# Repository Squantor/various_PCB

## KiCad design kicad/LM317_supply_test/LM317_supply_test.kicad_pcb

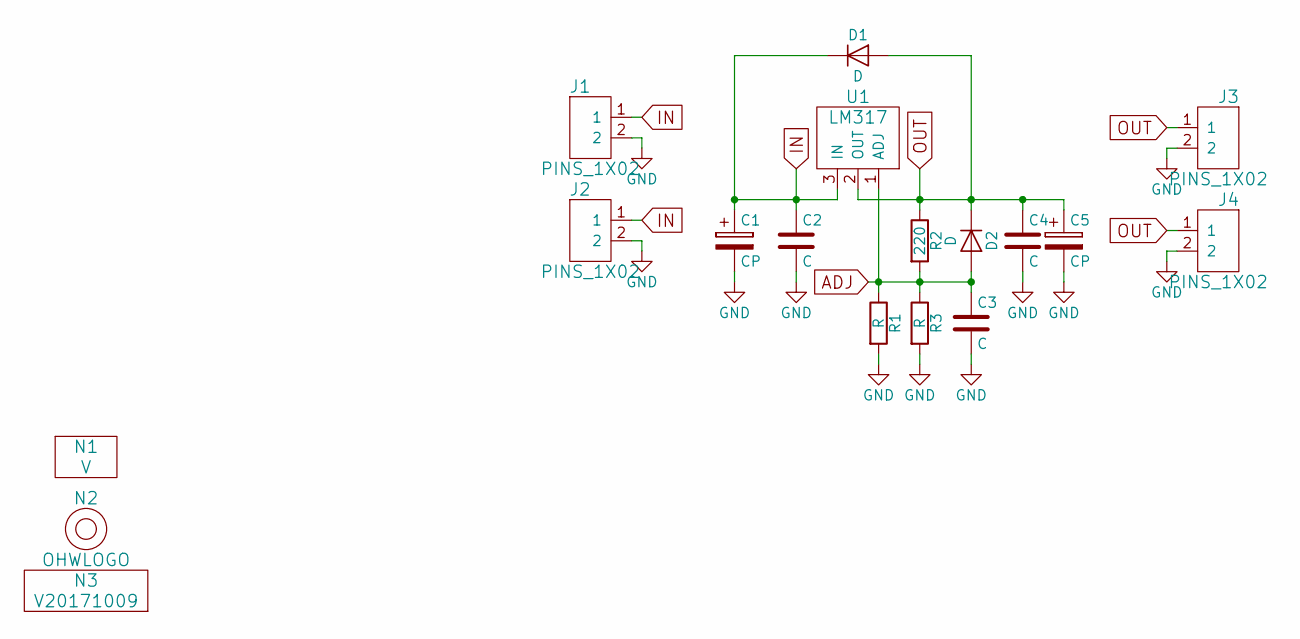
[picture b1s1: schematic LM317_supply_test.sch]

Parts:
C1, C5: CP; CPOL-05-06
C2, C3, C4: C; C_0805
D1, D2: D; MELF_D_0207
J1, J2, J3, J4: PINS_1X02; Header-0254-1X02-H010
N1: V; Label_Note_small
N2: OHWLOGO; OSHW-Symbol_6.7x6mm_SilkScreen
N3: V20171009; Label_version
R1, R3: R; R_0603_hand
R2: 220; R_0603_hand
U1: LM317; TO-263-D2PAK-3-3-viapad

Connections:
ADJ: C3.1, D2.2 (A), R1.1, R2.2, R3.1, U1.1 (ADJ)
GND: C1.2, C2.2, C3.2, C4.2, C5.2, J1.2, J2.2, J3.2, J4.2, R1.2, R3.2
IN: C1.1, C2.1, D1.1 (K), J1.1, J2.1, U1.3 (IN)
OUT: C4.1, C5.1, D1.2 (A), D2.1 (K), J3.1, J4.1, R2.1, U1.2 (OUT)

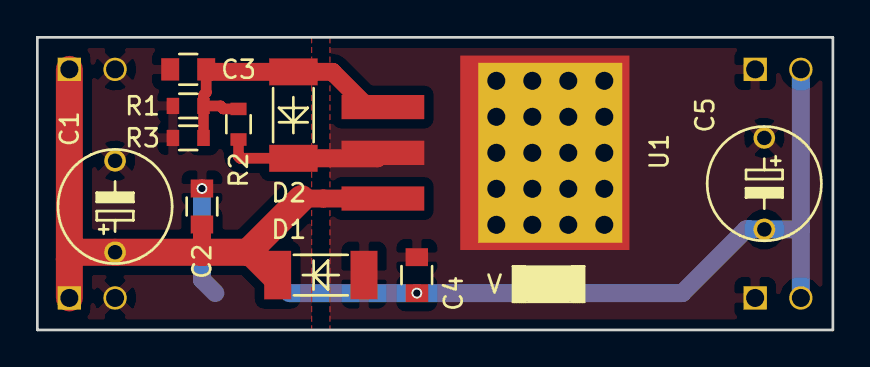
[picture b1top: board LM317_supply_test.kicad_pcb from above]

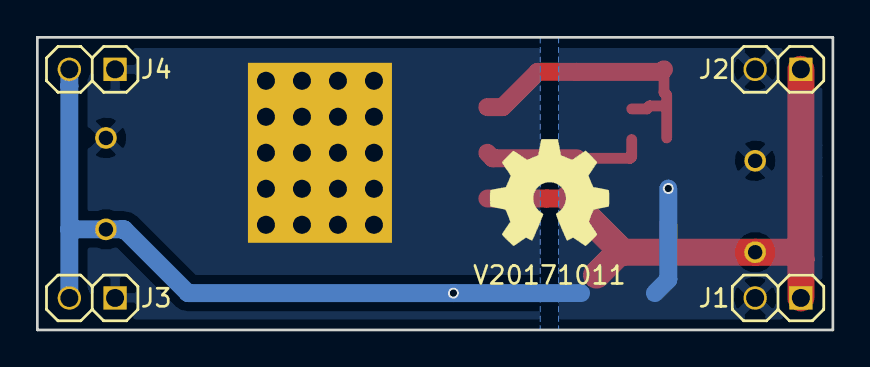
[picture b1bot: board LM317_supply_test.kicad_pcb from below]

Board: 2 copper layers, 44.2 x 16.3 mm, 18 parts (5 on the bottom side), 4 nets.

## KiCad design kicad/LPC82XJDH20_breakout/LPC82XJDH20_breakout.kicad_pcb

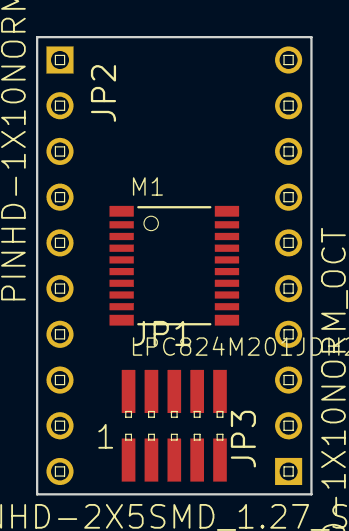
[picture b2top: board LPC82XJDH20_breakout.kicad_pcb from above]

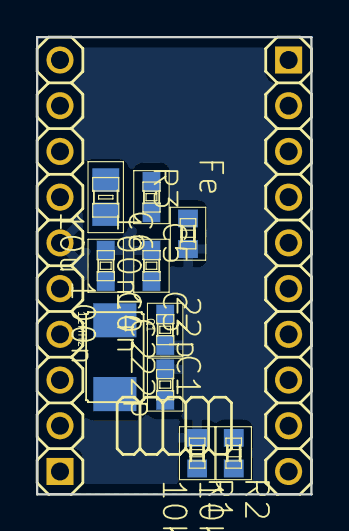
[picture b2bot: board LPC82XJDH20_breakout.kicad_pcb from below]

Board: 2 copper layers, 15.2 x 25.4 mm, 14 parts (10 on the bottom side), 20 nets, no tracks yet.

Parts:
C1, C2: 22p; SquantorRCL-C0603
C3: 10n; SquantorRCL-C0603
C4, C5: 100n; SquantorRCL-C0603
C6: 10u; SquantorRCL-C0805
JP1: PINHD-2X5SMD_1.27_SMD; SquantorConnectors-2X05_1.27_SMD
JP2, JP3: PINHD-1X10NORM_OCT; SquantorConnectors-1X10_NORMAL_OCT
M1: LPC824M201JDH20; SOT360
Q1: 12MHz; SquantorCrystal-CRYSTAL_5.0X3.2
R1, R2: 10k; SquantorRCL-R0603
R3: Fe; SquantorRCL-R0603

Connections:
GNDA: C5.2, C6.2, JP3.7, M1.17, R3.2
PIO0_0: JP3.9, M1.19
PIO0_1: JP3.2, M1.12
PIO0_2/SWDIO: JP1.1, JP2.8, M1.8, R2.2
PIO0_3/SWCLK: JP1.3, JP2.7, M1.7, R1.2
PIO0_4: JP2.6, M1.6
PIO0_5/reset: JP1.9, JP2.5, M1.5
PIO0_8: C1.1, JP3.4, M1.14, Q1.1
PIO0_9: C2.1, JP3.3, M1.13, Q1.2
PIO0_10: JP2.10, M1.10
PIO0_11: JP2.9, M1.9
PIO0_12: JP2.4, M1.4
PIO0_13: JP2.3, M1.3
PIO0_14: JP3.10, M1.20
PIO0_15: JP3.1, M1.11
PIO0_17: JP2.2, M1.2
PIO0_23: JP2.1, M1.1
VAA: C5.1, C6.1, JP3.8, M1.18
VDD: C3.2, C4.2, JP1.2, JP3.5, M1.15, R2.1
VSS: C1.2, C2.2, C3.1, C4.1, JP1.4, JP1.6, JP1.10, JP3.6, M1.16, R1.1, R3.1

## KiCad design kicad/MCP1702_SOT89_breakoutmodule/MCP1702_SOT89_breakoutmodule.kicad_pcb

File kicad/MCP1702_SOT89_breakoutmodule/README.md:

# MCP1702 breakout and module
This is a breakout for the MCP1702 LDO, it is breadboard friendly but two Molex Picoblade connectors make it also possible to use it in a cable. The MCP1702 has additional thermal vias and a large plane to help with power dissipation.

## TODO's
Still some things need to be done:
* schematic entry (Done)
* PCB layout (Done)
* Review with one night in between (Done)
* Produce at [OSHPARK](https://oshpark.com/shared_projects/njzrqEmi) (in progress)
* Assemble
* Test 
* update Readme.md with pictures and BOM
## BOM
TODO

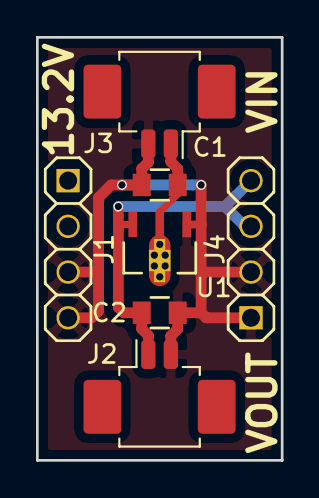
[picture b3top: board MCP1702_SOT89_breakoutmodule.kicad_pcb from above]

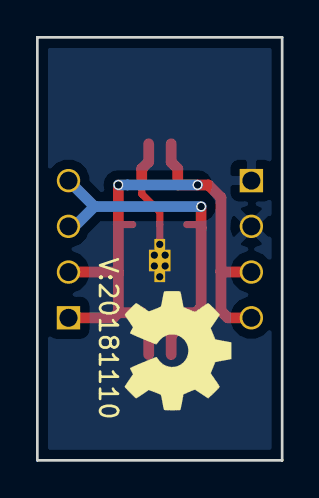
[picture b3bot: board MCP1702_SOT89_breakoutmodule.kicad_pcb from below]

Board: 2 copper layers, 13.6 x 23.5 mm, 9 parts (2 on the bottom side), 3 nets.

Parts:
C1, C2: C; C_0805
J1, J4: Conn_01x04; Header-0254-1X04-H010
J2, J3: Conn_01x02; Molex_PicoBlade_53261-0271_1x02-1MP_P1.25mm_Horizontal
N1: OHWLOGO; OSHW-Symbol_6.7x6mm_SilkScreen
N2: 20181110; Label_version
U1: MCP1702-MB; SOT89-ViaTab-Microchip-MB

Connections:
+12V: C1.1, J1.1, J1.2, J3.1, U1.2, U1.TAB
GND: C1.2, C2.2, J1.3, J1.4, J2.2, J3.2, J4.1, J4.2, U1.1
VDD: C2.1, J2.1, J4.3, J4.4, U1.3

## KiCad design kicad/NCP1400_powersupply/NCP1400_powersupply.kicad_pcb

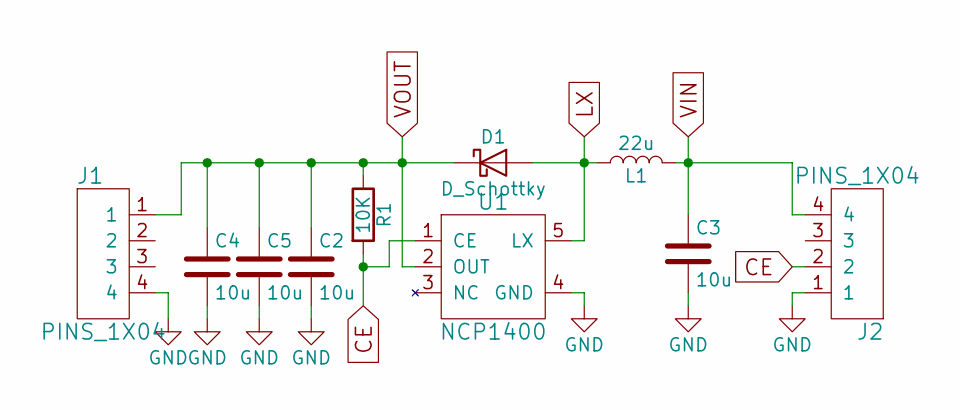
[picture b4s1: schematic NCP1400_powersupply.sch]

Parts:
C2, C3, C4, C5: 10u; C_0805
D1: D_Schottky; SOD-123-hand
J1, J2: PINS_1X04; Header-0254-1X04-H010
L1: 22u; TAIYO_YUDEN_NRS50XX
R1: 10K; R_0603_hand
U1: NCP1400; SN-SOT23-5

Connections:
CE: J2.2, R1.2, U1.1 (CE)
GND: C2.2, C3.2, C4.2, C5.2, J1.4, J2.1, U1.4 (GND)
LX: D1.2 (A), L1.1, U1.5 (LX)
VIN: C3.1, J2.4, L1.2
VOUT: C2.1, C4.1, C5.1, D1.1 (K), J1.1, R1.1, U1.2 (OUT)

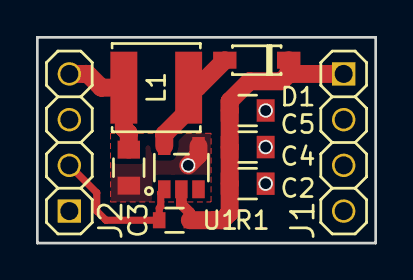
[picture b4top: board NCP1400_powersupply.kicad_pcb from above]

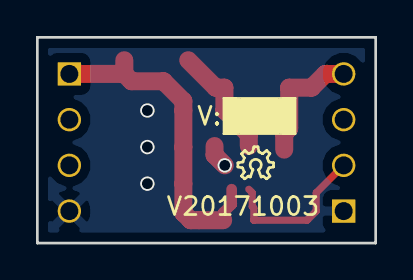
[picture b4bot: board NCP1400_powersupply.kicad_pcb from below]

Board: 2 copper layers, 18.8 x 11.4 mm, 13 parts (2 on the bottom side), 5 nets.

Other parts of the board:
N1: V20171003; Label_version
N2: OHWLOGO; ohw-logo-OSHW_6X70_NOTEXT
N3: V:; Label_Note_small

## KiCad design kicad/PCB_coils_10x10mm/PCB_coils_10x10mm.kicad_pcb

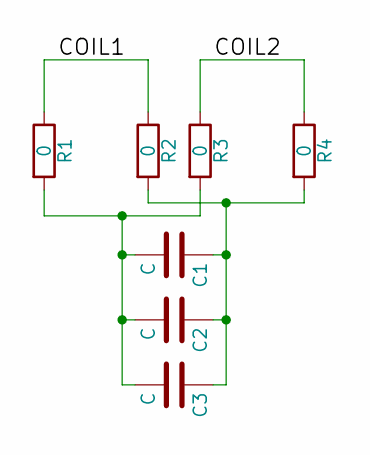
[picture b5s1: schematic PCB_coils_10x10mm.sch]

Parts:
C1, C2, C3: C; C_0805
R1, R2, R3, R4: 0; R_0603_hand

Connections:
/COIL1: R1.1, R2.1
/COIL2: R3.1, R4.1
unnamed: C1.1, C2.1, C3.1, R2.2, R4.2
unnamed: C1.2, C2.2, C3.2, R1.2, R3.2

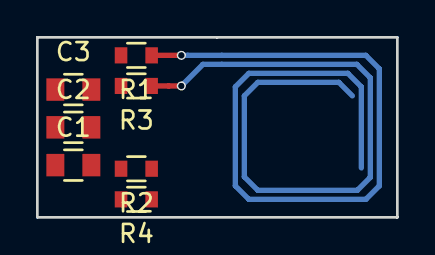
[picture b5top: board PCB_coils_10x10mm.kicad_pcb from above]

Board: 2 copper layers, 20.0 x 10.0 mm, 7 parts (0 on the bottom side), 4 nets.

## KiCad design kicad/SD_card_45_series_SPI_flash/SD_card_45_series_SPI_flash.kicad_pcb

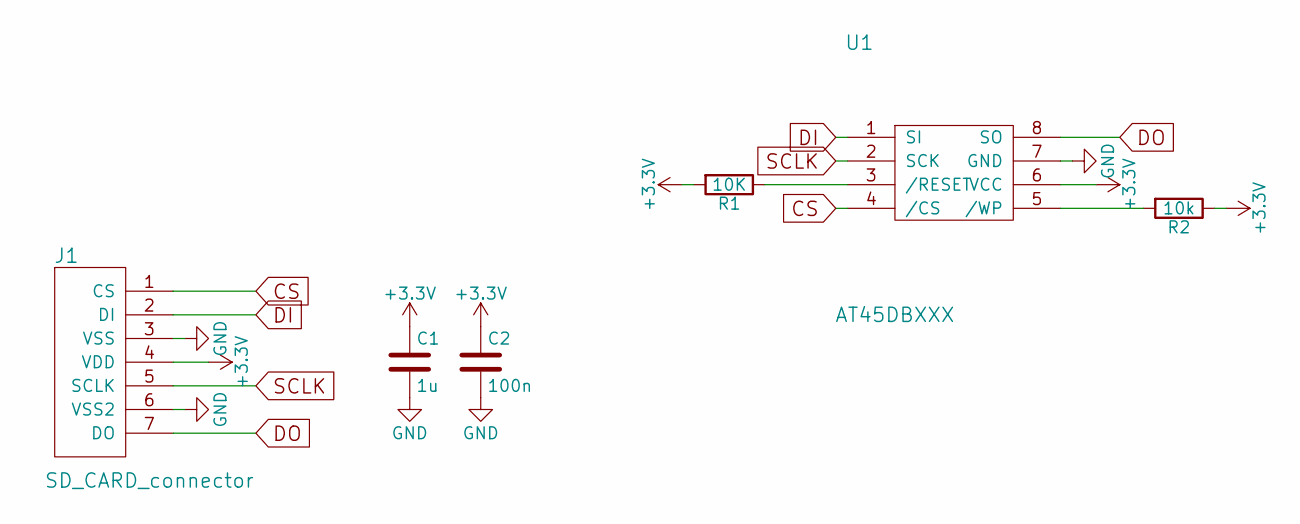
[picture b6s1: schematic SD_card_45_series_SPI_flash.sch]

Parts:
C1: 1u; C_0805
C2: 100n; C_0603
J1: SD_CARD_connector
R1: 10K; R_0603
R2: 10k; R_0603
U1: AT45DBXXX

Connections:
+3V3: C1.1, C2.1, J1.4 (VDD), R1.2, R2.1, U1.6 (VCC)
CS: J1.1 (CS), U1.4 (/CS)
DI: J1.2 (DI), U1.1 (SI)
DO: J1.7 (DO), U1.8 (SO)
GND: C1.2, C2.2, J1.3 (VSS), J1.6 (VSS2), U1.7 (GND)
unnamed: R1.1, U1.3 (/RESET)
unnamed: R2.2, U1.5 (/WP)
SCLK: J1.5 (SCLK), U1.2 (SCK)

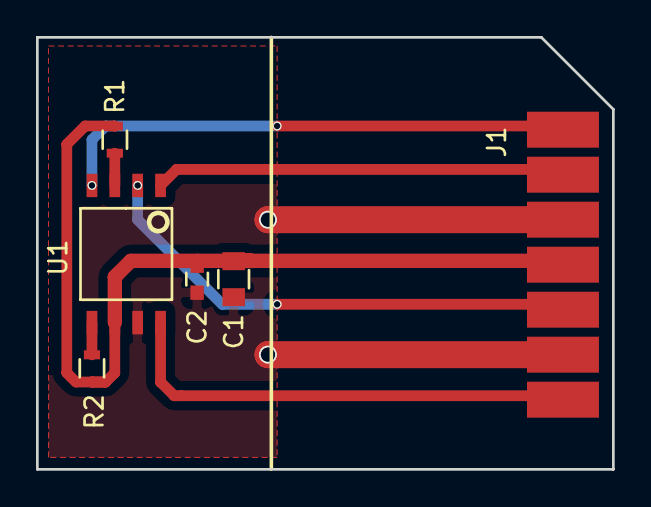
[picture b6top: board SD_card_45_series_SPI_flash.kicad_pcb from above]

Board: 2 copper layers, 32.0 x 24.0 mm, 6 parts (0 on the bottom side), 8 nets.

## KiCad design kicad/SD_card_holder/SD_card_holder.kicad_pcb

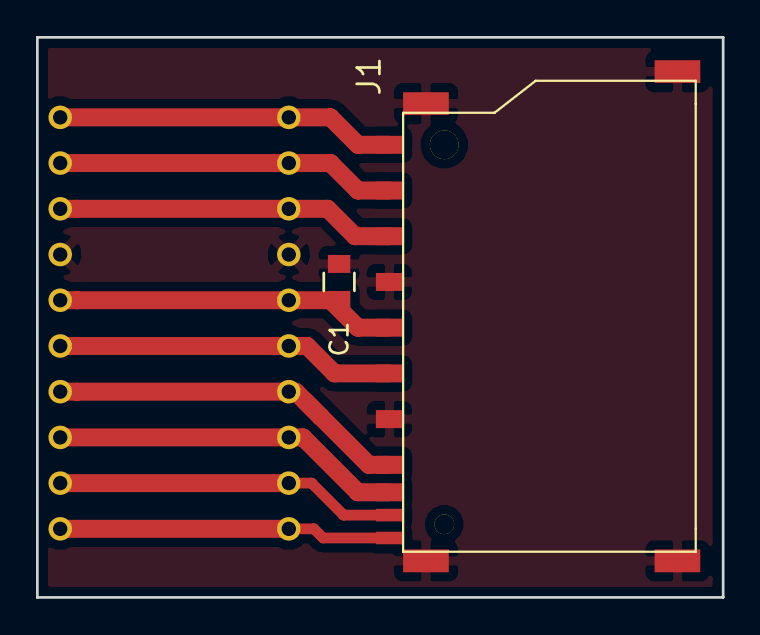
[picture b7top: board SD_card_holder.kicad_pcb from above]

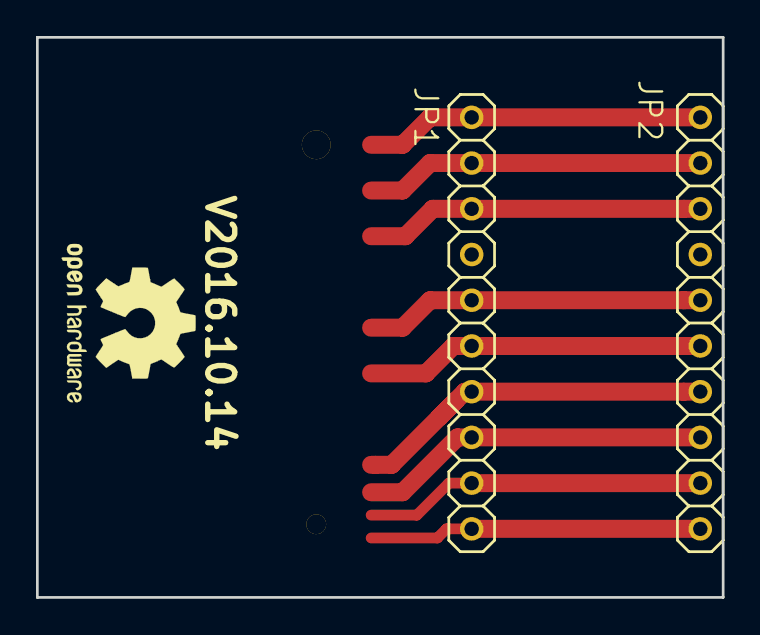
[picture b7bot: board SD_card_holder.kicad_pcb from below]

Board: 2 copper layers, 38.1 x 31.1 mm, 4 parts (2 on the bottom side), 10 nets.

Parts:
C1: 1u; C_0805
J1: SDCMF-10915W010; SquantorConnectors-SDCMF-10915W010
JP1, JP2: PINHD-1X10TH_NORMAL; SquantorConnectors-1X10_SMALL

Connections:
+3V3: C1.1, J1.4, JP1.5, JP2.5
GND: C1.2, J1.3, J1.6, J1.S1, J1.S2, J1.S3, J1.S4, JP1.4, JP2.4
unnamed: J1.1, JP1.2, JP2.2
unnamed: J1.2, JP1.3, JP2.3
unnamed: J1.5, JP1.6, JP2.6
unnamed: J1.7, JP1.7, JP2.7
unnamed: J1.8, JP1.8, JP2.8
unnamed: J1.9, JP1.1, JP2.1
unnamed: J1.CD, JP1.9, JP2.9
unnamed: J1.WP, JP1.10, JP2.10
